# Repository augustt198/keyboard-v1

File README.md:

<h1 align="center">KEYBOARD-V1</h1>

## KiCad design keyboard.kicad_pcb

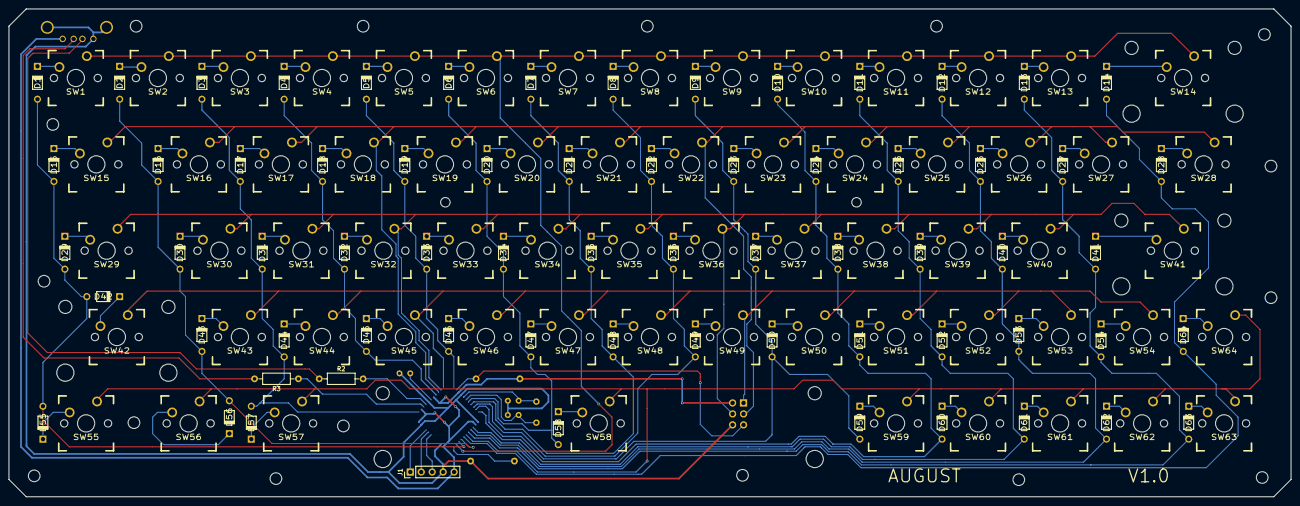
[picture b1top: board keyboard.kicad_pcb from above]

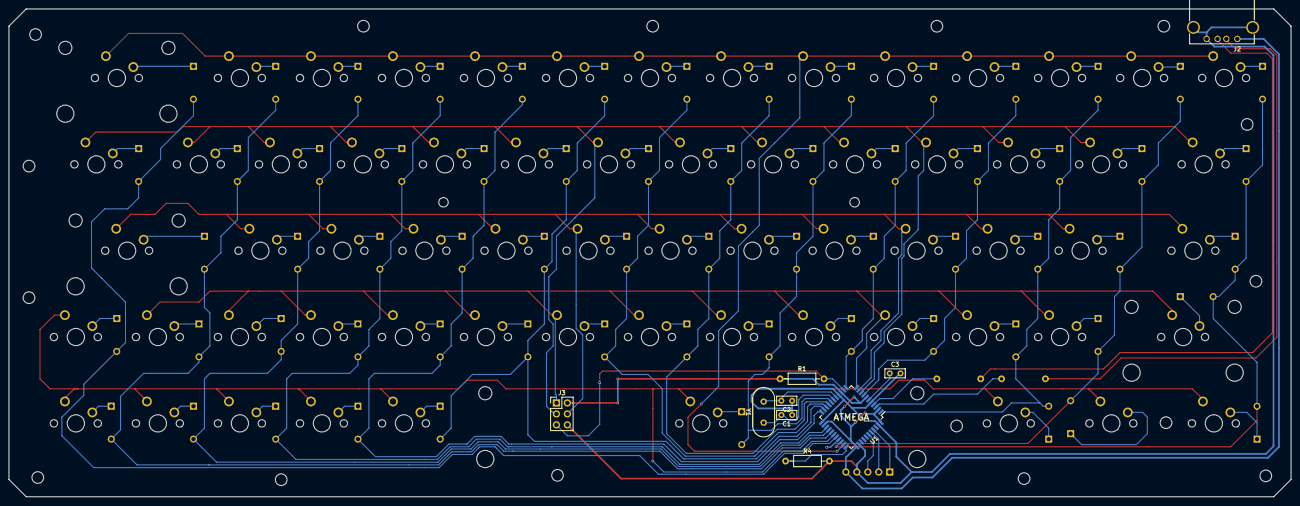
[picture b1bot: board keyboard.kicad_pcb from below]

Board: 2 copper layers, 297.0 x 113.0 mm, 140 parts (9 on the bottom side), 97 nets.

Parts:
C1, C2: 22pF; C_Rect_L4.6mm_W2.0mm_P2.50mm_MKS02_FKP02
C3: C; C_Rect_L4.6mm_W2.0mm_P2.50mm_MKS02_FKP02
D1, D2, D3, D4, D5, D6, D7, D8, D9, D10, D11, D12, D13, D14, D15, D16, D17, D18, D19, D20, D21, D22, D23, D24, D25, D26, D27, D28, D29, D30, D31, D32, D33, D34, D35, D36, D37, D38, D39, D40, D41, D42, D43, D44, D45, D46, D47, D48, D49, D50, D51, D52, D53, D54, D55, D56, D57, D58, D59, D60, D61, D62, D63, D64: D; DIODE
J1: CONN_01X05; Pin_Header_Straight_1x05_Pitch2.54mm
J2: USB_A
J3: CONN_02X03; Pin_Header_Straight_2x03_Pitch2.54mm
R1, R4: 10k; R_Axial_DIN0207_L6.3mm_D2.5mm_P10.16mm_Horizontal
R2, R3: 22; R_Axial_DIN0207_L6.3mm_D2.5mm_P10.16mm_Horizontal
SW1: KEY_ESC; CHERRY_PCB_100H
SW2: KEY_1; CHERRY_PCB_100H
SW3: KEY_2; CHERRY_PCB_100H
SW4: KEY_3; CHERRY_PCB_100H
SW5: KEY_4; CHERRY_PCB_100H
SW6: KEY_5; CHERRY_PCB_100H
SW7: KEY_6; CHERRY_PCB_100H
SW8: KEY_7; CHERRY_PCB_100H
SW9: KEY_8; CHERRY_PCB_100H
SW10: KEY_9; CHERRY_PCB_100H
SW11: KEY_0; CHERRY_PCB_100H
SW12: KEY_MINUS; CHERRY_PCB_100H
SW13: KEY_EQUAL; CHERRY_PCB_100H
SW14: KEY_DELETE; CHERRY_PCB_200H
SW15: KEY_TAB; CHERRY_PCB_150H
SW16: KEY_Q; CHERRY_PCB_100H
SW17: KEY_W; CHERRY_PCB_100H
SW18: KEY_E; CHERRY_PCB_100H
SW19: KEY_R; CHERRY_PCB_100H
SW20: KEY_T; CHERRY_PCB_100H
SW21: KEY_Y; CHERRY_PCB_100H
SW22: KEY_U; CHERRY_PCB_100H
SW23: KEY_I; CHERRY_PCB_100H
SW24: KEY_O; CHERRY_PCB_100H
SW25: KEY_P; CHERRY_PCB_100H
SW26: KEY_LBRACK; CHERRY_PCB_100H
SW27: KEY_RBRACK; CHERRY_PCB_100H
SW28: KEY_BACKSLH; CHERRY_PCB_150H
SW29: KEY_CAPS; CHERRY_PCB_175H
SW30: KEY_A; CHERRY_PCB_100H
SW31: KEY_S; CHERRY_PCB_100H
SW32: KEY_D; CHERRY_PCB_100H
SW33: KEY_F; CHERRY_PCB_100H
SW34: KEY_G; CHERRY_PCB_100H
SW35: KEY_H; CHERRY_PCB_100H
SW36: KEY_J; CHERRY_PCB_100H
SW37: KEY_K; CHERRY_PCB_100H
SW38: KEY_L; CHERRY_PCB_100H
SW39: KEY_SEMI; CHERRY_PCB_100H
SW40: KEY_APOS; CHERRY_PCB_100H
SW41: KEY_ENTER; CHERRY_PCB_225H
SW42: KEY_LSHIFT; CHERRY_PCB_200H
SW43: KEY_Z; CHERRY_PCB_100H
SW44: KEY_X; CHERRY_PCB_100H
SW45: KEY_C; CHERRY_PCB_100H
SW46: KEY_V; CHERRY_PCB_100H
SW47: KEY_B; CHERRY_PCB_100H
SW48: KEY_N; CHERRY_PCB_100H
SW49: KEY_M; CHERRY_PCB_100H
SW50: KEY_COMMA; CHERRY_PCB_100H
SW51: KEY_PERIOD; CHERRY_PCB_100H
SW52: KEY_SLASH; CHERRY_PCB_100H
SW53: KEY_UP; CHERRY_PCB_100H
SW54: KEY_RSHIFT; CHERRY_PCB_175H
SW55: KEY_LCTRL; CHERRY_PCB_125H
SW56: KEY_SPECIAL; CHERRY_PCB_125H
SW57: KEY_LALT; CHERRY_PCB_125H
SW58: KEY_SPACE; CHERRY_PCB_625H
SW59: KEY_RALT; CHERRY_PCB_100H
SW60: KEY_FN; CHERRY_PCB_100H
SW61: KEY_RCTRL; CHERRY_PCB_100H
SW62: KEY_LEFT; CHERRY_PCB_100H
SW63: KEY_DOWN; CHERRY_PCB_100H
SW64: KEY_RIGHT; CHERRY_PCB_100H
U1: ATMEGA32U4-AU; TQFP-44_10x10mm_Pitch0.8mm
Y1: 16mhz; Crystal_HC49-4H_Vertical

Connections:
/EXT1: J1.1, U1.41
/EXT2: J1.2, U1.40
/EXT3: J1.3, U1.39
/MISO: J3.1, SW42.1, SW43.1, SW44.1, SW45.1, SW46.1, SW47.1, SW48.1, SW49.1, SW50.1, SW51.1, SW52.1, SW53.1, SW54.1, U1.11
/MOSI: J3.4, SW29.1, SW30.1, SW31.1, SW32.1, SW33.1, SW34.1, SW35.1, SW36.1, SW37.1, SW38.1, SW39.1, SW40.1, SW41.1, U1.10
/RST: J3.5, R1.2, U1.13
/SCK: J3.3, SW15.1, SW16.1, SW17.1, SW18.1, SW19.1, SW20.1, SW21.1, SW22.1, SW23.1, SW24.1, SW25.1, SW26.1, SW27.1, SW28.1, U1.9
/matrix/col1: D1.1, D15.1, D29.1, D42.1, D55.1, U1.31
/matrix/col2: D2.1, D16.1, D30.1, D43.1, D56.1, U1.30
/matrix/col3: D3.1, D17.1, D31.1, D44.1, D57.1, U1.1
/matrix/col4: D4.1, D18.1, D32.1, D45.1, U1.8
/matrix/col5: D5.1, D19.1, D33.1, D46.1, U1.12
/matrix/col6: D6.1, D20.1, D34.1, D47.1, D58.1, U1.18
/matrix/col7: D7.1, D21.1, D35.1, D48.1, U1.19
/matrix/col8: D8.1, D22.1, D36.1, D49.1, U1.20
/matrix/col9: D9.1, D23.1, D37.1, D50.1, D59.1, U1.21
/matrix/col10: D10.1, D24.1, D38.1, D51.1, D60.1, U1.22
/matrix/col11: D11.1, D25.1, D39.1, D52.1, D61.1, U1.25
/matrix/col12: D12.1, D26.1, D40.1, D53.1, D62.1, U1.26
/matrix/col13: D13.1, D27.1, D41.1, D54.1, D63.1, U1.27
/matrix/col14: D14.1, D28.1, D64.1, U1.29
/matrix/row1: SW1.1, SW2.1, SW3.1, SW4.1, SW5.1, SW6.1, SW7.1, SW8.1, SW9.1, SW10.1, SW11.1, SW12.1, SW13.1, SW14.1, U1.32
/matrix/row5: SW55.1, SW56.1, SW57.1, SW58.1, SW59.1, SW60.1, SW61.1, SW62.1, SW63.1, SW64.1, U1.28
GND: C1.1, C2.1, C3.2, J1.4, J2.4, J2.5, J3.6, R4.2, U1.5, U1.15, U1.23, U1.35, U1.43
unnamed: C1.2, U1.17, Y1.1
unnamed: C2.2, U1.16, Y1.2
unnamed: C3.1, U1.6
unnamed: D1.2, SW1.2
unnamed: D2.2, SW2.2
unnamed: D3.2, SW3.2
unnamed: D4.2, SW4.2
unnamed: D5.2, SW5.2
unnamed: D6.2, SW6.2
unnamed: D7.2, SW7.2
unnamed: D8.2, SW8.2
unnamed: D9.2, SW9.2
unnamed: D10.2, SW10.2
unnamed: D11.2, SW11.2
unnamed: D12.2, SW12.2
unnamed: D13.2, SW13.2
unnamed: D14.2, SW14.2
unnamed: D15.2, SW15.2
unnamed: D16.2, SW16.2
unnamed: D17.2, SW17.2
unnamed: D18.2, SW18.2
unnamed: D19.2, SW19.2
unnamed: D20.2, SW20.2
unnamed: D21.2, SW21.2
unnamed: D22.2, SW22.2
unnamed: D23.2, SW23.2
unnamed: D24.2, SW24.2
unnamed: D25.2, SW25.2
unnamed: D26.2, SW26.2
unnamed: D27.2, SW27.2
unnamed: D28.2, SW28.2
unnamed: D29.2, SW29.2
unnamed: D30.2, SW30.2
unnamed: D31.2, SW31.2
unnamed: D32.2, SW32.2
unnamed: D33.2, SW33.2
unnamed: D34.2, SW34.2
unnamed: D35.2, SW35.2
unnamed: D36.2, SW36.2
unnamed: D37.2, SW37.2
unnamed: D38.2, SW38.2
unnamed: D39.2, SW39.2
unnamed: D40.2, SW40.2
unnamed: D41.2, SW41.2
unnamed: D42.2, SW42.2
unnamed: D43.2, SW43.2
unnamed: D44.2, SW44.2
unnamed: D45.2, SW45.2
unnamed: D46.2, SW46.2
unnamed: D47.2, SW47.2
unnamed: D48.2, SW48.2
unnamed: D49.2, SW49.2
unnamed: D50.2, SW50.2
unnamed: D51.2, SW51.2
unnamed: D52.2, SW52.2
unnamed: D53.2, SW53.2
unnamed: D54.2, SW54.2
unnamed: D55.2, SW55.2
unnamed: D56.2, SW56.2
unnamed: D57.2, SW57.2
unnamed: D58.2, SW58.2
unnamed: D59.2, SW59.2
unnamed: D60.2, SW60.2
unnamed: D61.2, SW61.2
unnamed: D62.2, SW62.2
unnamed: D63.2, SW63.2
unnamed: D64.2, SW64.2
unnamed: J2.2, R3.2
unnamed: J2.3, R2.1
unnamed: R2.2, U1.4
unnamed: R3.1, U1.3
unnamed: R4.1, U1.33
VCC: J1.5, J2.1, J3.2, R1.1, U1.2, U1.7, U1.14, U1.24, U1.34, U1.44

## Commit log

2017-05-21 More routing
2017-05-21 new net list
2017-05-22 checkpoint
2017-05-22 route some cols
2017-05-22 switch col 10 and 11
2017-05-24 almost done
2017-05-26 Add board edges
2017-08-09 exports
2017-08-15 pics
2017-08-15 README
2017-08-15 Organize old nets
2017-08-15 remove dupe file
